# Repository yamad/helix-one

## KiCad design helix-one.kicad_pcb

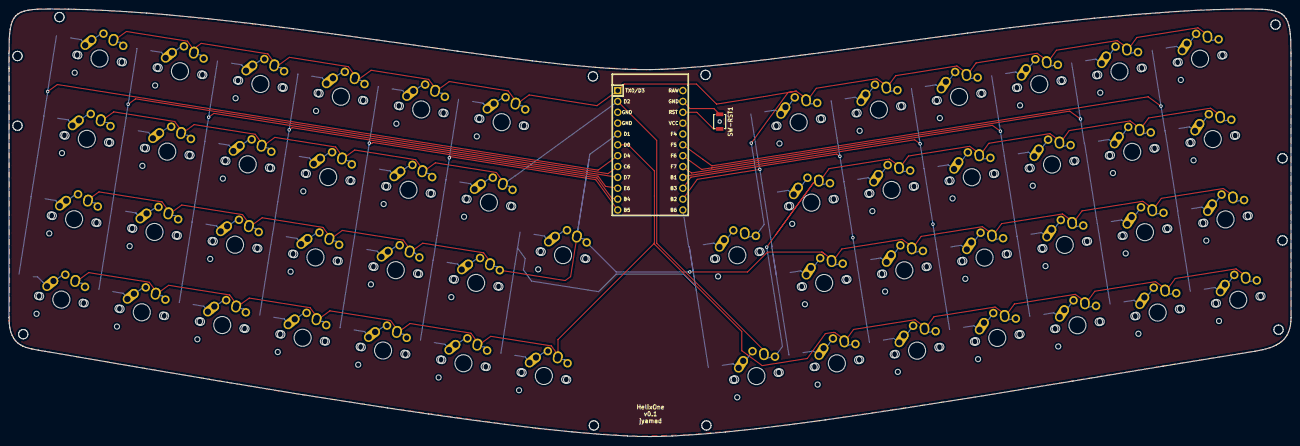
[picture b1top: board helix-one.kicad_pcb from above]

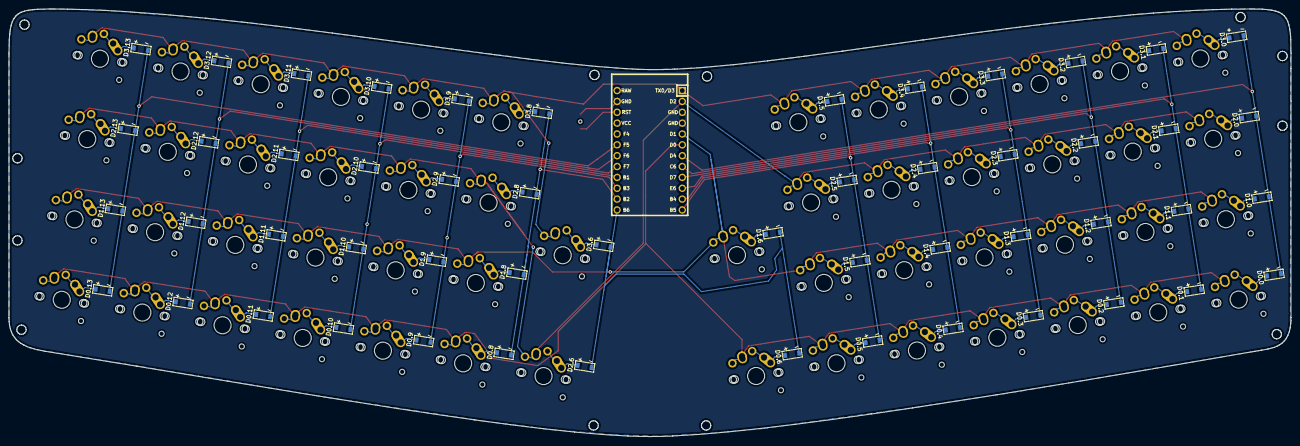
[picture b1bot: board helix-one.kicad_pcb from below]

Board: 2 copper layers, 300.0 x 100.1 mm, 106 parts (52 on the bottom side), 71 nets.

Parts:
D0.0, D0.1, D0.2, D0.3, D0.4, D0.5, D0.6, D0.8, D0.9, D0.10, D0.11, D0.12, D0.13, D1.0, D1.1, D1.2, D1.3, D1.4, D1.5, D1.6, D1.8, D1.9, D1.10, D1.11, D1.12, D1.13, D2.0, D2.1, D2.2, D2.3, D2.4, D2.5, D2.6, D2.8, D2.9, D2.10, D2.11, D2.12, D2.13, D3.0, D3.1, D3.2, D3.3, D3.4, D3.5, D3.6, D3.8, D3.9, D3.10, D3.11, D3.12, D3.13: DIODE; D_SOD-123_side_legend
SW0.0, SW0.1, SW0.2, SW0.3, SW0.4, SW0.5, SW0.6, SW0.8, SW0.9, SW0.10, SW0.11, SW0.12, SW0.13, SW1.0, SW1.1, SW1.2, SW1.3, SW1.4, SW1.5, SW1.6, SW1.8, SW1.9, SW1.10, SW1.11, SW1.12, SW1.13, SW2.0, SW2.1, SW2.2, SW2.3, SW2.4, SW2.5, SW2.6, SW2.8, SW2.9, SW2.10, SW2.11, SW2.12, SW2.13, SW3.0, SW3.1, SW3.2, SW3.3, SW3.4, SW3.5, SW3.6, SW3.8, SW3.9, SW3.10, SW3.11, SW3.12, SW3.13: SWITCH_PUSH; MX-Alps-Choc-1U-NoLED
SW-RST1: SWITCH_PUSH; SW_SPST_B3U-1000P-B
U1: ARDUINO_PRO_MICRO; ArduinoProMicro

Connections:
/COL0: D0.0.2, D1.0.2, D2.0.2, D3.0.2, U1.7
/COL1: D0.1.2, D1.1.2, D2.1.2, D3.1.2, U1.8
/COL2: D0.2.2, D1.2.2, D2.2.2, D3.2.2, U1.9
/COL3: D0.3.2, D1.3.2, D2.3.2, D3.3.2, U1.10
/COL4: D0.4.2, D1.4.2, D2.4.2, D3.4.2, U1.11
/COL5: D0.5.2, D1.5.2, D2.5.2, D3.5.2, U1.12
/COL6: D0.6.2, D1.6.2, D2.6.2, D3.6.2, U1.13
/COL8: D0.8.2, D1.8.2, D2.8.2, D3.8.2, U1.14
/COL9: D0.9.2, D1.9.2, D2.9.2, D3.9.2, U1.15
/COL10: D0.10.2, D1.10.2, D2.10.2, D3.10.2, U1.16
/COL11: D0.11.2, D1.11.2, D2.11.2, D3.11.2, U1.17
/COL12: D0.12.2, D1.12.2, D2.12.2, D3.12.2, U1.18
/COL13: D0.13.2, D1.13.2, D2.13.2, D3.13.2, U1.19
/ROW0: SW0.0.1, SW0.1.1, SW0.2.1, SW0.3.1, SW0.4.1, SW0.5.1, SW0.6.1, SW0.8.1, SW0.9.1, SW0.10.1, SW0.11.1, SW0.12.1, SW0.13.1, U1.6
/ROW1: SW1.0.1, SW1.1.1, SW1.2.1, SW1.3.1, SW1.4.1, SW1.5.1, SW1.6.1, SW1.8.1, SW1.9.1, SW1.10.1, SW1.11.1, SW1.12.1, SW1.13.1, U1.5
/ROW2: SW2.0.1, SW2.1.1, SW2.2.1, SW2.3.1, SW2.4.1, SW2.5.1, SW2.6.1, SW2.8.1, SW2.9.1, SW2.10.1, SW2.11.1, SW2.12.1, SW2.13.1, U1.2
/ROW3: SW3.0.1, SW3.1.1, SW3.2.1, SW3.3.1, SW3.4.1, SW3.5.1, SW3.6.1, SW3.8.1, SW3.9.1, SW3.10.1, SW3.11.1, SW3.12.1, SW3.13.1, U1.1
GND: SW-RST1.1, U1.3, U1.4, U1.23
unnamed: D0.0.1, SW0.0.2
unnamed: D0.1.1, SW0.1.2
unnamed: D0.2.1, SW0.2.2
unnamed: D0.3.1, SW0.3.2
unnamed: D0.4.1, SW0.4.2
unnamed: D0.5.1, SW0.5.2
unnamed: D0.6.1, SW0.6.2
unnamed: D0.8.1, SW0.8.2
unnamed: D0.9.1, SW0.9.2
unnamed: D0.10.1, SW0.10.2
unnamed: D0.11.1, SW0.11.2
unnamed: D0.12.1, SW0.12.2
unnamed: D0.13.1, SW0.13.2
unnamed: D1.0.1, SW1.0.2
unnamed: D1.1.1, SW1.1.2
unnamed: D1.2.1, SW1.2.2
unnamed: D1.3.1, SW1.3.2
unnamed: D1.4.1, SW1.4.2
unnamed: D1.5.1, SW1.5.2
unnamed: D1.6.1, SW1.6.2
unnamed: D1.8.1, SW1.8.2
unnamed: D1.9.1, SW1.9.2
unnamed: D1.10.1, SW1.10.2
unnamed: D1.11.1, SW1.11.2
unnamed: D1.12.1, SW1.12.2
unnamed: D1.13.1, SW1.13.2
unnamed: D2.0.1, SW2.0.2
unnamed: D2.1.1, SW2.1.2
unnamed: D2.2.1, SW2.2.2
unnamed: D2.3.1, SW2.3.2
unnamed: D2.4.1, SW2.4.2
unnamed: D2.5.1, SW2.5.2
unnamed: D2.6.1, SW2.6.2
unnamed: D2.8.1, SW2.8.2
unnamed: D2.9.1, SW2.9.2
unnamed: D2.10.1, SW2.10.2
unnamed: D2.11.1, SW2.11.2
unnamed: D2.12.1, SW2.12.2
unnamed: D2.13.1, SW2.13.2
unnamed: D3.0.1, SW3.0.2
unnamed: D3.1.1, SW3.1.2
unnamed: D3.2.1, SW3.2.2
unnamed: D3.3.1, SW3.3.2
unnamed: D3.4.1, SW3.4.2
unnamed: D3.5.1, SW3.5.2
unnamed: D3.6.1, SW3.6.2
unnamed: D3.8.1, SW3.8.2
unnamed: D3.9.1, SW3.9.2
unnamed: D3.10.1, SW3.10.2
unnamed: D3.11.1, SW3.11.2
unnamed: D3.12.1, SW3.12.2
unnamed: D3.13.1, SW3.13.2
unnamed: SW-RST1.2, U1.22

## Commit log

2020-07-18 initial commit - helix one keyboard
